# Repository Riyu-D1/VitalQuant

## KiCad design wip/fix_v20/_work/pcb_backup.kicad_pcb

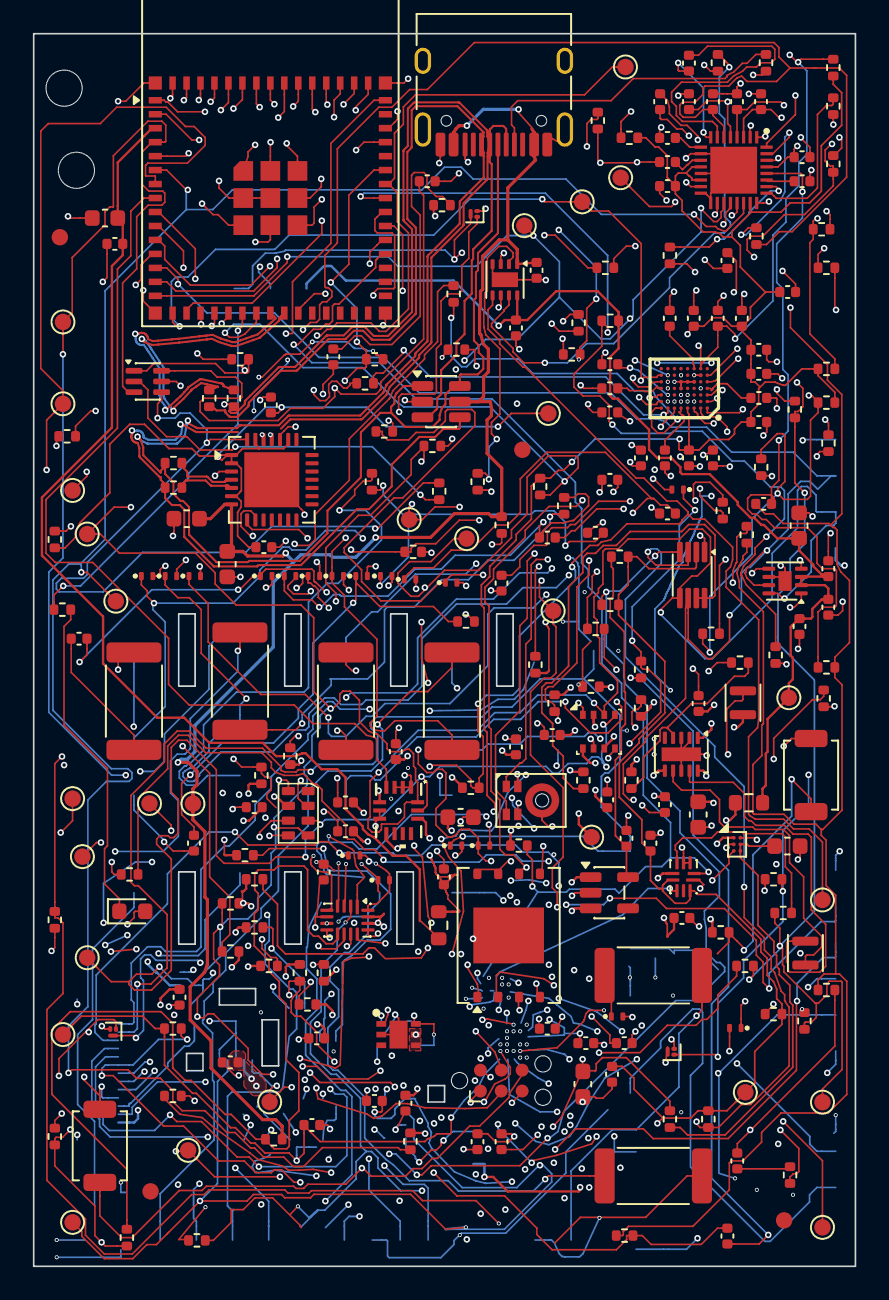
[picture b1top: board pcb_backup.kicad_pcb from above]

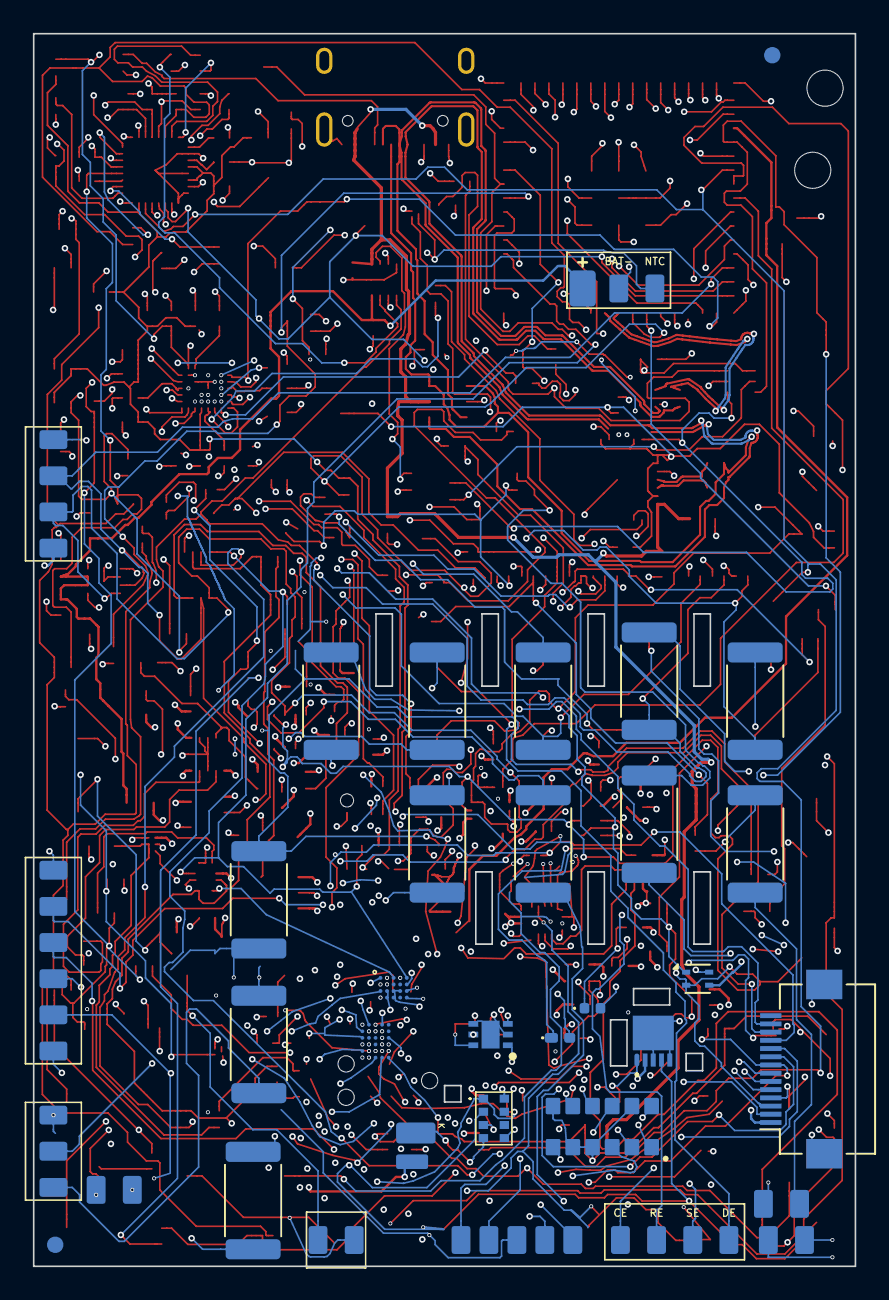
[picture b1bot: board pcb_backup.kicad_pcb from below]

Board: 8 copper layers, 50.0 x 75.0 mm, 299 parts (35 on the bottom side), 191 nets.

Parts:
C1, C47: 4.7u; C_0603_1608Metric
C2, C20: 4.7u; C_0402_1005Metric
C3, C4, C6, C11, C14, C16, C19, C26, C32, C33, C42, C43, C63, C64, C66, C79, C80, C82, C83, C84: 1u; C_0402_1005Metric
C7, C45: 22u; C_0603_1608Metric
C8, C13, C15, C18, C24, C25, C27, C28, C29, C36, C37, C38, C39, C40, C41, C50, C51, C56, C57, C58, C59, C60, C61, C62, C76, C77, C78, C81, C86, C88, C90, C91: 100n; C_0402_1005Metric
C9, C30, C87: 10u; C_0402_1005Metric
C10: 1u; C_0603_1608Metric
C21, C22, C23, C55, C68, C69, C70: 470n; C_0402_1005Metric
C34: 47n; C_0402_1005Metric
C35: 4.7n; C_0402_1005Metric
C44, C89: 10u; C_0603_1608Metric
C46: 2.2u; C_0402_1005Metric
C48, C49, C52, C53: 2.2n; C_0402_1005Metric
C54, C67: 15n; C_0402_1005Metric
C65: 1.5n; C_0402_1005Metric
C85: 47u; C_0603_1608Metric
D1, D2, D3, D4, D5, D6, D7, D8, D9, D21, D22, D23, D24, D26, D27, D28, D29, D30: TPD1E10B06; TPD1E10B06_DPY
D10: JB3030UWT-B-H50EA0000-1Z000001; NF2W757G
D11: SFH4053; LED_0402_1005Metric
D12: XL0603NRC730; LED_0603_1608Metric
D25: KT-0603G; LED_0603_1608Metric
FID1, FID2, FID3, FID4, FID5, FID6: FID; Fiducial_1mm
H1, H2: M2; MountingHole_2.2mm_M2
J1: USB-C; USB_C_Receptacle_HRO_TYPE-C-31-M-12
J2: LiPo pads; Pads_LiPo
J3: FSR pads; Pads_FSR
J5: ECG pads; Pads_ECG
J6: EDA pads; Pads_EDA
J7: Chest bioZ; Pads_BIOZ
J8: TC2030; Tag-Connect_TC2030-IDC-NL_2x03_P1.27mm_Vertical
J9: I2C tail pads; Pads_1x04
J10: Optical tail pads; Pads_1x06
J11: Sweat site; Pads_1x03
J12: FH12-14S; Hirose_FH12-14S-0.5SH_1x14-1MP_P0.50mm_Horizontal
J13: MX ECG pads; Pads_1x02
L1: 0.47u; L_DFE201612E
L2: 1.0u; L_DFE201612E
Q1, Q2, Q4: CSD13380F3T; Texas_PicoStar_DFN-3_0.69x0.60mm
Q3: BC847BS,115; SOT-363_SC-70-6
R1, R2: 5.1k; R_0402_1005Metric
R3: 1.5k; R_0402_1005Metric
R5, R6, R7, R8, R9, R11, R14, R49, R52, R53, R60, R61, R65, R67, R68, R69, R70, R71, R72, R73, R74, R98, R100, R101, R112, R113, R115, R116, R117: 10k; R_0402_1005Metric
R10, R13, R39, R40, R41, R42, R62, R84, R85, R86, R87: 1k; R_0402_1005Metric
R12: 10; R_0402_1005Metric
R15, R16, R17: 1M; R_0402_1005Metric
R18: 200k; R_0402_1005Metric
R19, R20, R21, R22: 2.2k; R_0402_1005Metric
R23: 560k; R_0402_1005Metric
R24, R25, R44, R46, R48, R50, R59, R99, R107, R108, R110: 100k; R_0402_1005Metric
R26, R27, R28, R29: 10M; R_0402_1005Metric
R30, R31: 40.2k; R_0402_1005Metric
R32, R33, R34, R35, R36, R76, R77, R78, R79, R80, R81, R82, R83, R118, R119, R120, R121, R122: 51k; R_2512_6332Metric
R43, R45: 5.11M; R_0402_1005Metric
R47, R109: 100; R_0402_1005Metric
R51: 150k; R_0402_1005Metric
R63: 22.1k; R_0402_1005Metric
R64: 47.5k; R_0402_1005Metric
R66: 301k; R_0402_1005Metric
R75: 27.0k; R_0402_1005Metric
R88: 150; R_0402_1005Metric
R89, R90, R91, R92, R95, R96, R97, R102, R103, R104, R105, R106, R114: 0; R_0402_1005Metric
R93, R94: 0; R_0603_1608Metric
SW1, SW2: TS-1088; SW_SPST_TS-1088-xR020
TP1: VBUS; TestPoint_Pad_D1.0mm
TP2: VBAT; TestPoint_Pad_D1.0mm
TP3: +3V3; TestPoint_Pad_D1.0mm
TP4: +1V8; TestPoint_Pad_D1.0mm
TP5: TX_5V; TestPoint_Pad_D1.0mm
TP6: VDD_CP2102; TestPoint_Pad_D1.0mm
TP7, TP8: GND; TestPoint_Pad_D1.0mm
TP9: ESP_EN; TestPoint_Pad_D1.0mm
TP10: ESP_IO0; TestPoint_Pad_D1.0mm
TP11: ESP_TX; TestPoint_Pad_D1.0mm
TP12: ESP_RX; TestPoint_Pad_D1.0mm
TP13: I2C_SDA; TestPoint_Pad_D1.0mm
TP14: I2C_SCL; TestPoint_Pad_D1.0mm
TP15: I2C_SDA_1V8; TestPoint_Pad_D1.0mm
TP16: I2C_SCL_1V8; TestPoint_Pad_D1.0mm
TP17: SPI_SCK; TestPoint_Pad_D1.0mm
TP18: SPI_MOSI; TestPoint_Pad_D1.0mm
TP19: SPI_MISO; TestPoint_Pad_D1.0mm
TP20: CS_ADS1292; TestPoint_Pad_D1.0mm
TP21: CS_AFE4900; TestPoint_Pad_D1.0mm
TP22: CS_AD5940; TestPoint_Pad_D1.0mm
TP23: CS_FLASH; TestPoint_Pad_D1.0mm
TP24: ADS1292_DRDY; TestPoint_Pad_D1.0mm
TP25: AFE4900_ADC_RDY; TestPoint_Pad_D1.0mm
TP26: EXP_INT; TestPoint_Pad_D1.0mm
TP27: CHG_STAT; TestPoint_Pad_D1.0mm
TP28: RTC_INT; TestPoint_Pad_D1.0mm
U1: ESP32-S3-MINI-1-N4R2; ESP32_S3_MINI_1
U2: BQ25170DSGR; Texas_DSG0008A_WSON-8-1EP_2x2mm_P0.5mm_EP0.9x1.6mm
U3: TPS63802DLAR; WSON-10-1EP_2x3mm_P0.5mm_EP0.84x2.4mm
U4: TPS7A2018PDBVR; SOT-23-5
U5: CP2102N-A02-GQFN28R; QFN-28-1EP_5x5mm_P0.5mm_EP3.35x3.35mm
U6: AFE4900YZR; BGA30N40P5X6_260X210X50
U7: AD5940BCBZ-RL7; BGA56C40P8X7_416X356X55
U8: ADS1292RIRSMT; QFN40P400X400X100-33N-D
U9: PCA9306DCUR; VSSOP-8_2.3x2mm_P0.5mm
U10: AS7341-DLGM; AS7341DLGT
U11, U20: TMP117AIDRVR; TMP117_DRV_NOPASTE
U12: MLX90632SLD-DCB-100-SP; MLX90632SLDDCB100SP
U13: BME280; Bosch_LGA-8_2.5x2.5mm_P0.65mm_ClockwisePinNumbering
U14: LSM6DSV80XTR; QFN_LSM6DSV80XTR_STM
U15: TPS61240YFFR; TPS61240_YFF
U16: SFH 7072; SFH7072
U17: MAX17048G+T10; TDFN-8-1EP_2x2mm_P0.5mm_EP0.8x1.2mm
U18: W25Q512JVEIQ; W25Q512_WSON8
U19: TCA6408ARSVR; TCA6408A_RSV
U21: USBLC6-2SC6; SOT-23-6
U22: MAX86141ENP+; MAX86141_WLP20
U23: SHT45-AD1B; SHT45_DFN4
U24: RV-3028-C7; RV3028C7
U25: IM69D130
U26: SN74AXC2T245RSWR; Texas_RSW0010A_UQFN-10_1.4x1.8mm_P0.4mm

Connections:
+1V8: C36.1, C86.1, C87.1, C88.1, C90.1, R21.1, R22.1, R66.1, R97.2, TP4.1, U9.2, U10.1, U22.C2 (VDD_DIG), U22.D2 (VDD_ANA), U26.7, U26.10
+1V8_LDO: C6.1, R97.1, U4.5
+3V3: C4.1, C37.1, C38.1, C39.1, C40.1, C41.1, C45.1, C59.1, C60.1, C61.1, C76.1, C77.1, C78.1, C81.1, C84.1, C91.1, D10.1, J3.1, J8.1, J9.1, J12.1, R5.1, R6.1, R7.1, R18.1, R19.1, R20.1, R23.1, R47.1, R49.1, R52.1, R53.1, R60.1, R65.1, R74.1, R94.1, R95.1, R98.1, R99.1, R109.1, R112.1, R113.1, R117.1, TP3.1, U3.6, U4.1, U4.3, U11.5, U12.2, U13.2, U13.6, U13.8, U14.5, U14.8, U14.12, U18.3, U18.7, U18.8, U19.14, U19.15, U20.4, U20.5, U23.3, U24.7, U25.2, U26.6
+3V3_ANA: C11.1, C13.1, C16.1, C18.1, C28.1, C29.1, C43.1, C79.1, C80.1, R12.1, R15.1, R26.1, R28.1, R95.2, R116.1, U6.A4, U6.C1, U6.C4, U7.A4, U7.F2, U7.F3, U8.12, U8.14, U8.23
+3V3_ESP: C7.1, C8.1, R94.2, U1.3
AD5940_GPIO0: U1.18, U7.F5
AD5940_RESET: R11.1, U7.F1, U19.4
ADS1292_DRDY: R99.2, TP24.1, U1.6, U8.22
ADS1292_PWDN: R14.1, U8.15, U19.3
ADS_GPIO1: R100.1, U8.26
ADS_GPIO2: R101.1, U8.25
AFE4900_ADC_RDY: TP25.1, U1.25, U6.F4
AFE4900_RESETZ: R9.1, U6.E1, U19.2
AFE_BG: C15.1, U6.D2
AFE_CLK: R10.1, U6.F1
AFE_INM: C57.2, R45.2, U6.A1
AFE_INP: C56.2, R43.2, U6.B1
AFE_N_AC: D5.1, R36.2, R46.1
AFE_N_PAD: J5.5, R36.1
AFE_N_SER: C57.1, R46.2
AFE_P_AC: D4.1, R35.2, R44.1
AFE_P_PAD: J5.4, R35.1
AFE_P_SER: C56.1, R44.2
AIN4_LPF0: C26.1, U7.B4
AVDD_REG: C42.1, U7.D8
BIOZ_FN: C68.2, U7.D2
BIOZ_FN_PAD: J7.2, R81.1
BIOZ_FP: R84.2, U7.B3
BIOZ_FP_PAD: J7.1, R80.1
BIOZ_SN: C70.2, U7.A3
BIOZ_SN_PAD: J7.4, R83.1
BIOZ_SP: C69.2, U7.B5
BIOZ_SP_PAD: J7.3, R82.1
CE0: R39.2, U7.A7
CE_ISO: C54.2, D6.1, R39.1
CE_SURGE: C54.1, R76.2
CHG_DIS: Q2.1, R59.1, U19.10
CHG_ISET: R3.1, U2.2
CHG_PG: R60.2, U1.11, U2.6
CHG_STAT: R49.2, TP27.1, U2.5, U19.8
CHG_VSET: R75.1, U2.7
CP_DTR: Q3.4, R70.1, U5.28
CP_RST: R62.2, U5.9
CP_RTS: Q3.1, R71.1, U5.24
CP_RX: R72.2, U5.25
CP_TX: R73.1, U5.26
CP_VBUS: R63.2, R64.1, U5.8
CS_AD5940: R7.2, TP22.1, U1.19, U7.F7
CS_ADS1292: R98.2, TP20.1, U1.14, U8.18
CS_AFE4900: R116.2, TP21.1, U1.22, U6.E3
CS_FLASH: R52.2, TP23.1, U1.20, U18.1
CS_MAX86178: R117.2, U1.34, U22.A5 (CSB), U26.2
DE0: R42.2, U7.B6
DE_SURGE: D9.1, R42.1, R79.2
DVDD_REG: C23.1, U7.G3
ECG1_PAD: J5.1, R32.1
ECG2_PAD: J5.2, R33.1
ECG_N: C51.1, C53.1, D2.1, R31.2, R33.2, U8.5
ECG_P: C50.1, C52.1, D1.1, R30.2, R32.2, U8.6
EDA_CE_PAD: J6.1, R76.1
EDA_DE_PAD: J6.4, R79.1
EDA_RE_PAD: J6.2, R78.1
EDA_SE_PAD: J6.3, R77.1
ESP_EN: C64.1, J8.5, Q3.6, R5.2, SW1.1, TP9.1, U1.45, U19.1
ESP_IO0: J8.6, Q3.3, R6.2, SW2.1, TP10.1, U1.4
ESP_RX: J8.4, R73.2, TP12.1, U1.40
ESP_TX: J8.3, R72.1, TP11.1, U1.39
EXP_INT: R53.2, TP26.1, U1.7, U19.11
FB_3V3: R23.2, R24.1, U3.4
FN_ISO: C68.1, D22.1, R85.2
FN_SURGE: R81.2, R85.1
FP_ISO: C67.2, D21.1, R84.1
FP_SURGE: C67.1, R80.2
FSR_ADC: J3.2, R8.1, U1.5
GAUGE_ALRT: R74.2, U1.10, U17.5
GND: C1.2, C2.2, C3.2, C4.2, C6.2, C7.2, C8.2, C9.2, C10.2, C11.2, C13.2, C14.2, C15.2, C16.2, C18.2, C19.2, C20.2, C21.2, C22.2, C23.2, C24.2, C25.2, C26.2, C28.2, C29.2, C30.2, C32.2, C33.2, C36.2, C37.2, C38.2, C39.2, C40.2, C41.2, C42.2, C43.2, C44.2, C45.2, C46.2, C47.2, C48.2, C49.2, C52.2, C53.2, C58.2, C59.2, C60.2, C61.2, C62.2, C63.2, C64.2, C66.2, C76.2, C77.2, C78.2, C79.2, C80.2, C81.2, C82.2, C83.2, C84.2, C85.2, C86.2, C87.2, C88.2, C89.2, C90.2, C91.2, D1.2, D2.2, D3.2, D4.2, D5.2, D6.2, D7.2, D8.2, D9.2, D21.2, D22.2, D23.2, D24.2, D25.2, D26.2, D27.2, D28.2, D29.2, D30.2, J1.A1, J1.A12, J1.B1, J1.B12, J1.SH, J2.2, J8.2, J9.4, J12.4, Q1.2, Q2.2, Q4.2, R1.2, R2.2, R3.2, R8.2, R9.2, R10.2, R11.2, R14.2, R16.2, R24.2, R25.2, R27.2, R29.2, R48.2, R51.2, R59.2, R61.2, R64.2, R66.2, R75.2, R100.2, R101.2, R108.2, R110.2, R115.2, SW1.2, SW2.2, TP7.1, TP8.1, U1.1, U1.2, U1.42, U1.43, U1.46, U1.47, U1.48, U1.49, U1.50, U1.51, U1.52, U1.53, U1.54, U1.55, U1.56, U1.57, U1.58, U1.59, U1.60, U1.61, U1.62, U1.63, U1.64, U1.65, U2.4, U2.9, U3.2, U3.3, U3.8, U3.11, U4.2, U5.3, U5.29, U6.B4, U6.D1, U6.D5, U7.C4, U7.D5, U7.E3, U7.E4, U7.E5, U7.E6, U8.10, U8.13, U8.16, U8.17, U8.24, U8.33, U9.1, U10.3, U10.5, U11.2, U11.4, U11.7, U12.3, U12.5, U12.6, U13.1, U13.5, U13.7, U14.1, U14.2, U14.3, U14.6, U14.7, U15.A2, U17.1, U17.4, U17.6, U17.9, U18.4, U18.9, U19.6, U19.16, U20.2, U20.7, U21.2, U22.C3 (GND_DIG), U22.C4 (GND_ANA), U22.D3 (PGND), U23.4, U24.5, U24.8, U25.4, U25.5, U26.1, U26.3, U26.4
I2C_SCL: J9.3, J12.3, R20.2, TP14.1, U1.13, U9.6, U11.1, U13.4, U14.13, U17.7, U19.12, U20.1, U23.2, U24.3
I2C_SCL_1V8: R22.2, TP16.1, U9.3, U10.2, U12.4
I2C_SDA: J9.2, J12.2, R19.2, TP13.1, U1.12, U9.5, U11.6, U13.3, U14.14, U17.8, U19.13, U20.6, U23.1, U24.4
I2C_SDA_1V8: R21.2, TP15.1, U9.4, U10.8, U12.1
IN1N: C49.1, R28.2, R29.1, R68.2, U8.3
IN1N_AC: C51.2, R68.1
IN1P: C48.1, R26.2, R27.1, R67.2, U8.4
IN1P_AC: C50.2, R67.1
IOVDD: C19.1, R12.2, U7.G2
IR_AN: D11.1, R47.2
IR_GATE: Q1.1, R48.1, U19.7
IR_K: D11.2, Q1.3
J11_CE: J11.3, R122.1
J11_RE: J11.2, R121.1
J11_WE: J11.1, R120.1
J13_INM: J13.2, R119.1
J13_INP: J13.1, R118.1
LDR: D10.2, U10.4
LED1_K: J10.1, J12.5, U22.D1 (LED1_DRV)
LED2_K: J10.2, J12.6, U22.C1 (LED2_DRV)
LED3_K: J10.3, J12.7, U22.B1 (LED3_DRV)
LED_A: D25.1, R88.2
LED_AN: J10.4, J12.8, R114.2
LSM6_INT1: U1.8, U14.4
MAX86178_INT: R113.2, U1.35, U22.B2 (INT)
MIC_CLK: U1.36, U25.3
MIC_DAT: U1.37, U25.1
MISO_AD: R91.1, U7.E8
MISO_ADS: R89.1, U8.21
MISO_AFE: R90.1, U6.E2
MISO_FL: R92.1, U18.2
MISO_MX: R106.1, U26.5
MX_ECG_INM: D30.1, R119.2
MX_ECG_INP: D29.1, R118.2
MX_SDO_1V8: U22.A3 (SDO), U26.8
MX_VREF: C83.1, U22.B5 (VREF)
NIR730_GATE: Q4.1, R110.1, U7.E1
NIR_AN: D12.1, R109.2
NIR_K: D12.2, Q4.3
PD2_INM: U6.B3, U16.10
PD2_INP: U6.B2, U16.3
PD_A: J10.6, J12.10, U22.C5 (PD_GND)
PD_INM: U6.A3, U16.2
PD_INP: U6.A2, U16.1
PD_K: J10.5, J12.9, U22.D5 (PD1_IN)
PGA1N: C34.1, U8.1
PGA1P: C34.2, U8.2
PGA2N: C35.1, U8.7
PGA2P: C35.2, U8.8
Q3_B1: Q3.2, R70.2
Q3_B2: Q3.5, R71.2
RC0_0: C27.1, U7.C8
RC0_1: C27.2, U7.B8
RCAL0: R13.1, U7.C1
RCAL1: R13.2, U7.B1
RE0: R41.2, U7.A8
RESP_MODN: R31.1, U8.32
RESP_MODP: R30.1, U8.31
RE_SURGE: D8.1, R41.1, R78.2
RLDINV: C65.2, R17.2, U8.28
RLDOUT: C65.1, R17.1, R43.1, R45.1, R69.2, U8.30
RLDREF: C66.1, R15.2, R16.1, U8.29
RLD_CLAMP: D3.1, R34.2, R69.1
RLD_PAD: J5.3, R34.1
RTC_INT: R112.2, TP28.1, U24.2
RTC_VBK: R115.1, U24.6
SE0: C55.2, U7.A6
SE_ISO: C55.1, D7.1, R40.2
SE_SURGE: R40.1, R77.2
SN_ISO: C70.1, D24.1, R87.2
SN_SURGE: R83.2, R87.1
SPARE_IN: R107.2, R108.1, U1.38
SPI_MISO: R89.2, R90.2, R91.2, R92.2, R106.2, TP19.1, U1.17
SPI_MOSI: TP18.1, U1.15, U6.F2, U7.E7, U8.19, U18.5, U22.A4 (SDI)
SPI_SCK: TP17.1, U1.16, U6.F3, U7.F8, U8.20, U18.6, U22.A2 (SCLK)
SP_ISO: C69.1, D23.1, R86.2
SP_SURGE: R82.2, R86.1
STATUS_LED: R88.1, U1.21
SWEAT_CE: D28.1, J12.13, R122.2, U7.A1
SWEAT_RE: D27.1, J12.12, R121.2, U7.A2
SWEAT_WE: D26.1, J12.11, R120.2, U7.C5
SW_L1: L1.1, U3.9
SW_L2: L1.2, U3.7
TMP117_ALERT: R65.2, U1.9, U11.3
TS: J2.3, Q2.3, R61.1, U2.3
TX1: U6.D4, U16.6
TX2: U6.E5, U16.12
TX3: U6.E4, U16.8
TX4: U6.C5, U16.9
TX5_EN: R25.1, U15.C1, U19.5
TX_5V: C14.1, C89.1, R96.2, R114.1, TP5.1, U6.F5, U16.4, U16.5, U16.7, U16.11, U22.A1 (VLED)
TX_5V_RAW: C47.1, R96.1, U15.B2, U15.C2
TX_SW: L2.2, U15.B1
USB_CC1: J1.A5, R1.1
USB_CC2: J1.B5, R2.1
USB_DM: J1.A7, J1.B7, R103.1, R105.1, U21.3, U21.4
USB_DM_CP: R105.2, U5.5
USB_DM_S3: R103.2, U1.23
USB_DP: J1.A6, J1.B6, R102.1, R104.1, U21.1, U21.6
USB_DP_CP: R104.2, U5.4
USB_DP_S3: R102.2, U1.24
VBAT: C2.1, C3.1, C58.1, C82.1, C85.1, J2.1, R93.1, R107.1, TP2.1, U2.8, U17.2, U17.3
VBAT_SYS: C44.1, C46.1, L2.1, R93.2, U3.1, U3.10, U15.A1
VBIAS0: C25.1, U7.C7
VBIAS_CAP: C22.1, U7.D1
VBUS: C1.1, C10.1, C63.1, J1.A4, J1.A9, J1.B4, J1.B9, R50.1, R63.1, TP1.1, U2.1, U5.7, U21.5
VBUS_DET: R50.2, R51.1, U19.9
VCAP1: C32.1, U8.11
VCAP2: C33.1, U8.27
VDD_CP2102: C9.1, C62.1, R62.1, TP6.1, U5.1, U5.2, U5.6, U5.23, U5.27
VREF2: R18.2, U9.7, U9.8
VREFP: C30.1, U8.9
VREF_1V82: C20.1, U7.A5
VREF_2V5: C21.1, U7.D7
VZERO0: C24.1, U7.B7

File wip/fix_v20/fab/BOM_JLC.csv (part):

"Comment","Designator","Footprint","LCSC Part #","Quantity","Manufacturer","Manufacturer Part Number"
"4.7u","C1, C47","C_0603_1608Metric","C69335","2","Samsung Electro-Mechanics","CL10A475KA8NQNC"
"4.7u","C2, C20","C_0402_1005Metric","C23733","2","Samsung Electro-Mechanics","CL05A475MP5NRNC"
"1u","C3, C4, C6, C11, C14, C16, C19, C26, C32, C33, C42, C43, C64, C66, C80, C82, C83, C84","C_0402_1005Metric","C52923","18","Samsung Electro-Mechanics","CL05A105KA5NQNC"
"22u","C7, C45","C_0603_1608Metric","C86295","2","Samsung Electro-Mechanics","CL10A226MP8NUNE"
"100n","C8, C13, C15, C18, C24, C25, C27, C28, C29, C36, C37, C38, C39, C40, C41, C50, C51, C56, C57, C58, C59, C60, C61, C62, C76, C77, C78, C81, C86, C88, C90, C91","C_0402_1005Metric","C1525","32","Samsung Electro-Mechanics","CL05B104KO5NNNC"
"10u","C9","C_0402_1005Metric","C77000","1","muRata","GRM155R61A106ME44D"
"1u","C10","C_0603_1608Metric","C15849","1","Samsung Electro-Mechanics","CL10A105KB8NNNC"
"470n","C21, C22, C23, C55, C68, C69, C70","C_0402_1005Metric","C480644","7","Samsung Electro-Mechanics","CL05A474KO5NNNC"
"10u","C30, C87","C_0402_1005Metric","C15525","2","Samsung Electro-Mechanics","CL05A106MQ5NUNC"
"47n","C34","C_0402_1005Metric","C2183123","1","Murata Electronics","GRM155R71H473KE14J"
"4.7n","C35","C_0402_1005Metric","C106208","1","YAGEO","CC0402KRX7R9BB472"
"10u","C44, C89","C_0603_1608Metric","C19702","2","Samsung Electro-Mechanics","CL10A106KP8NNNC"
"2.2u","C46","C_0402_1005Metric","C107369","1","Samsung Electro-Mechanics","CL05A225KP5NSNC"
"2.2n","C48, C49, C52, C53","C_0402_1005Metric","C106861","4","YAGEO","CC0402KRX7R9BB222"
"15n","C54, C67","C_0402_1005Metric","C501821","2","FH (Guangdong Fenghua Advanced Tech)","0402B153K500NT"
"1u","C63, C79","C_0402_1005Metric","C52923","2","Samsung Electro-Mechanics","CL05A105KA5NQNC"
"1.5n","C65","C_0402_1005Metric","C107022","1","YAGEO","CC0402KRX7R9BB152"
"47u","C85","C_0603_1608Metric","C730416","1","Samsung Electro-Mechanics","CL10A476MQ8QRNC"
"TPD1E10B06","D1, D2, D3, D4, D5, D6, D7, D8, D9, D21, D22, D23, D24, D26, D27, D28, D29, D30","TPD1E10B06_DPY","C48260","18","Texas Instruments","TPD1E10B06DPYR"
"NF2W757G-F1","D10","NF2W757G","","1","Nichia","NF2W757G-F1 (consigned)"
"SFH4053","D11","LED_0402_1005Metric","C2900307","1","OSRAM Opto Semicon","SFH 4053"
"XL0603NRC730","D12","LED_0603_1608Metric","","1","Sealand/XL","XL0603NRC730 (consigned)"
"KT-0603G","D25","LED_0603_1608Metric","C12624","1","Hubei KENTO Elec","KT-0603G"
"1N5819WS","D33","D_SOD-323","C191023","1","Guangdong Hottech","1N5819WS"
"USB-C","J1","USB_C_Receptacle_HRO_TYPE-C-31-M-12","C165948","1","Korean Hroparts Elec","TYPE-C-31-M-12"
"FH12-14S","J12","Hirose_FH12-14S-0.5SH_1x14-1MP_P0.50mm_Horizontal","C5378715","1","HRS(Hirose)","FH12-14S-0.5SH(55)"
"0.47u","L1","L_DFE201612E","C668312","1","Murata Electronics","DFE201612E-R47M=P2"
"1.0u","L2","L_DFE201612E","C337892","1","Murata Electronics","DFE201612E-1R0M=P2"
"CSD13380F3T","Q1, Q2, Q4","Texas_PicoStar_DFN-3_0.69x0.60mm","C2871092","3","Texas Instruments","CSD13380F3T"
"BC847BS,115","Q3","SOT-363_SC-70-6","C156292","1","Diodes Incorporated","BC847BS-7-F"
"AO3401A","Q6","SOT-23","C15127","1","Alpha & Omega Semicon","AO3401A"
"5.1k","R1, R2","R_0402_1005Metric","C25905","2","UNI-ROYAL(Uniroyal Elec)","0402WGF5101TCE"
"1.5k","R3","R_0402_1005Metric","C25867","1","UNI-ROYAL","0402WGF1501TCE"
"10k","R5, R6, R7, R8, R9, R11, R14, R49, R52, R53, R60, R65, R67, R68, R69, R70, R71, R72, R73, R74, R98, R100, R101, R112, R113, R115, R116, R117","R_0402_1005Metric","C25744","28","UNI-ROYAL(Uniroyal Elec)","0402WGF1002TCE"
"NTC 10k B3380","R61","R_0402_1005Metric","C77131","1","Murata","NCP15XH103F03RC"
"1k","R10, R13, R39, R40, R41, R42, R62, R84, R85, R86, R87","R_0402_1005Metric","C11702","11","UNI-ROYAL(Uniroyal Elec)","0402WGF1001TCE"
"10","R12","R_0402_1005Metric","C25077","1","UNI-ROYAL","0402WGF100JTCE"
"1M","R15, R16, R17","R_0402_1005Metric","C26083","3","UNI-ROYAL","0402WGF1004TCE"
"200k","R18","R_0402_1005Metric","C25764","1","UNI-ROYAL","0402WGF2003TCE"
"2.2k","R19, R20, R21, R22","R_0402_1005Metric","C25879","4","UNI-ROYAL(Uniroyal Elec)","0402WGF2201TCE"
"560k","R23","R_0402_1005Metric","C137958","1","YAGEO","RC0402FR-07560KL"
"100k","R24, R25, R44, R46, R48, R50, R59, R99, R110, R123","R_0402_1005Metric","C25741","10","UNI-ROYAL(Uniroyal Elec)","0402WGF1003TCE"
"10M","R26, R27, R28, R29","R_0402_1005Metric","C26086","4","UNI-ROYAL","0402WGJ0106TCE"
"40.2k","R30, R31","R_0402_1005Metric","C25893","2","UNI-ROYAL","0402WGF4022TCE"
"51k","R32, R33, R34, R35, R36, R76, R77, R78, R79, R80, R81, R82, R83","R_2512_6332Metric","C6669155","13","YAGEO","RV2512FK-0751KL"
"5.11M","R43, R45","R_0402_1005Metric","C283954","2","Vishay Intertech","CRCW04025M11FKED"
"100","R47, R109","R_0402_1005Metric","C25076","2","UNI-ROYAL","0402WGF1000TCE"
"150k","R51","R_0402_1005Metric","C25755","1","UNI-ROYAL(Uniroyal Elec)","0402WGF1503TCE"
"22.1k","R63","R_0402_1005Metric","C853138","1","YAGEO","RT0402BRE0722K1L"
"47.5k","R64","R_0402_1005Metric","C25896","1","UNI-ROYAL(Uniroyal Elec)","0402WGF4752TCE"
"301k","R66","R_0402_1005Metric","C6097400","1","Walsin Tech Corp","MR04X3013FTL"
"27.0k","R75","R_0402_1005Metric","C25771","1","UNI-ROYAL","0402WGF2702TCE"
"150","R88","R_0402_1005Metric","C25082","1","UNI-ROYAL(Uniroyal Elec)","0402WGF1500TCE"
"0","R89, R90, R91, R92, R95, R96, R97, R102, R103, R106, R114","R_0402_1005Metric","C17168","11","UNI-ROYAL(Uniroyal Elec)","0402WGF0000TCE"
"0","R94","R_0603_1608Metric","C21189","1","UNI-ROYAL(Uniroyal Elec)","0603WAF0000T5E"
"51k","R118, R119, R120, R121, R122","R_2512_6332Metric","C6669155","5","YAGEO","RV2512FK-0751KL"
"TS-1088","SW1, SW2","SW_SPST_TS-1088-xR020","C720477","2","XUNPU","TS-1088-AR02016"
"ESP32-S3-WROOM-1-N16R8","U1","ESP32_S3_WROOM_1","C2913202","1","Espressif Systems","ESP32-S3-WROOM-1-N16R8"
"BQ25170DSGR","U2","Texas_DSG0008A_WSON-8-1EP_2x2mm_P0.5mm_EP0.9x1.6mm","C5208201","1","Texas Instruments","BQ25170DSGR"
"TPS63802DLAR","U3","WSON-10-1EP_2x3mm_P0.5mm_EP0.84x2.4mm","C2845237","1","Texas Instruments","TPS63802DLAR"
"TPS7A2018PDBVR","U4","SOT-23-5","C963430","1","Texas Instruments","TPS7A2018PDBVR"
"CP2102N-A02-GQFN28R","U5","QFN-28-1EP_5x5mm_P0.5mm_EP3.35x3.35mm","C964632","1","SKYWORKS/SILICON LABS","CP2102N-A02-GQFN28R"
"AFE4900YZR","U6","BGA30N40P5X6_260X210X50","C2651595","1","Texas Instruments","AFE4900YZR"
"AD5940BCBZ-RL7","U7","BGA56C40P8X7_416X356X55","C650308","1","Analog Devices","AD5940BCBZ-RL7"
"ADS1292RIRSMT","U8","QFN40P400X400X100-33N-D","C882777","1","Texas Instruments","ADS1292RIRSMT"
"PCA9306DCUR","U9","VSSOP-8_2.3x2mm_P0.5mm","C33196","1","Texas Instruments","PCA9306DCUR"
"AS7341-DLGM","U10","AS7341DLGT","C2649486","1","ams OSRAM","AS7341-DLGM"
"TMP117AIDRVR","U11, U20","TMP117_DRV_NOPASTE","C699536","2","Texas Instruments","TMP117AIDRVR"
"MLX90632SLD-DCB-100-SP","U12","MLX90632SLDDCB100SP","C5349491","1","Melexis","MLX90632SLD-DCB-100-RE"
"BME280","U13","Bosch_LGA-8_2.5x2.5mm_P0.65mm_ClockwisePinNumbering","C92489","1","Bosch Sensortec","BME280"
"LSM6DSV80XTR","U14","QFN_LSM6DSV80XTR_STM","C46898862","1","STMicroelectronics","LSM6DSV80XTR"
"TPS61240YFFR","U15","TPS61240_YFF","C2070904","1","Texas Instruments","TPS61240YFFR"
"SFH 7072","U16","SFH7072","C2655172","1","OSRAM Opto Semicon","SFH 7072"
"MAX17048G+T10","U17","TDFN-8-1EP_2x2mm_P0.5mm_EP0.8x1.2mm","C2682616","1","Analog Devices Inc./Maxim Integrated","MAX17048G+T10"
"W25Q512JVEIQ","U18","W25Q512_WSON8","C2986165","1","Winbond Elec","W25Q512JVEIQ"
"TCA6408ARSVR","U19","TCA6408A_RSV","C2649390","1","Texas Instruments","TCA6408ARSVR"
"USBLC6-2SC6","U21","SOT-23-6","C7519","1","STMicroelectronics","USBLC6-2SC6"
"MAX86141ENP+","U22","MAX86141_WLP20","C5328762","1","Analog Devices Inc./Maxim Integrated","MAX86141ENP+T"
"SHT45-AD1B","U23","SHT45_DFN4","C6705435","1","Sensirion","SHT45-AD1B-R3"
"RV-3028-C7","U24","RV3028C7","C2829066","1","Micro Crystal","RV-3028-C7"
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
